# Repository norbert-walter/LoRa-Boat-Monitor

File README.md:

## LoRa Boat Monitor

Image: LoRa Boat Monitor

Project home page: https://open-boat-projects.org/en/lora-bootsmonitor/

The LoRa boat monitor is used to monitor the boat when it is absent. Various measured values are continuously recorded at freely adjustable time intervals and transferred to the [LoRaWAN](https://www.lora-wan.de/) forwarded. The data is from the TTN server ([The Thinks Network](https://thethingsnetwork.org/)) received in Amsterdam and cached and then sent to [Ubidots](https://ubidots.com/) forwarded as a web frontend. The data transmission is secured by encryption up to Ubidots. The measured data is displayed in Ubidots and various notifications can be sent by email when measured values are exceeded.

There are a large number of [LoRa gateways](https://thethingsnetwork.org/map) which can receive the sent measurement data and forward it to the TTN server. Many LoRa gateways are run by private individuals on a non-profit basis. Anyone who wants can operate their own gateway and make it available to the general public. The radio technology uses the license-free frequency range around 868 MHz and uses a special transmission technology (chirp) to achieve large ranges of up to 50 km at low data rates. The ranges depend on the type of transmission, the antenna height and the environment. In built-up areas such as cities, typical ranges of 1… 4 km are possible. In open environments such as lakes and the sea, up to 50 km can be reached. There are no costs for data transmission when sending LoRa telegrams. This is the big difference to other long range transmission technologies like [SIGFOX](https://www.sigfox.com/) and mobile data networks such as 3G / 4G / 5G. If no LoRa gateway is within range, a simple 1-channel or 3-channel LoRa gateway can be set up with the same board. Only a few components are then left out and a different firmware used. Alternatively, the measured values can also be sent directly to Ubidots via WLAN, provided that a WLAN is within range.

Image: LoRa data transmission Semtech GmbH

Image: Block diagram LoRa boat monitor

## The LoRa boat monitor has the following functions:

* 10… 32V supply voltage
* 1.2W power consumption
* LoRa transmitter and receiver with OLED display
* 868 MHz, SF7… SF12, 100 mW transmission power
* Dynamic spreeding factor adjustable SF7… FS10
* Supports channel 0...7 dynamic and fix
* Data transfer rate: 0.3 to 50 kbit / s
* Max. Telegram length for user data: 200 bytes
* Range: built-up area 1… 4km, open area up to 50km
* LoRa transmission interval 30s… 2.1h
* One-channel, three-channel and eight-channel modes can be set
* Feeding the data into The Thinks Network (TTN)
* Parameterization of the LoRa boat monitor possible via return channel (channel, SF, transmission interval, relay)
* WLAN (2.4 GHz) for alternative data transmission
* Web interface for operation
* Firmware update possible via WLAN and Internet
* GPS sensor for geographic location coordinates
* BME280 for measuring temperature, humidity and air pressure
* 1x battery voltage measurement (0… 32V service battery)
* 1x potential-free alarm contact eg for bilge and door monitoring
* 2x tank sensors (0 ... 180 Ohm) with percentage display
* Calibratable tank and voltage sensors
* 1x Reais output for potential-free switching of loads with specified time (5min ... 21h) up to 3A (12V or 230V)
* 2x 1Wire connection for temperature sensors DS18B20 for battery monitoring and refrigerator
* Monitoring and alerting via Ubidots web frontend
* Alerting by e-mail if limit values are exceeded via Ubidots
* Automatic data storage for the last 31 days at Ubidots
* Use of cheap embedded modules
* No SMD components on the board and easy to build
* Board can be ordered here:[https://aisler.net/p/GEIYWWXZ](https://aisler.net/p/GEIYWWXZ)
* Android app

## Create your own code

You have the option of creating your own code using the online [software development environment Gitpod](https://gitpod.io/#https://github.com/norbert-walter/LoRa-Boat-Monitor). Follow this link and a finished development environment similar to PlatformIO will be created that runs in your browser with all code components. To compile the software, enter ***bash run*** in the terminal. In the workspace you will find the compiled binary code under ***.pio/build/heltec_wifi_lora_32_V2/firmware.bin***. With a right click you can download the binary file. You need a account for Gitpod.
## Device flash process

With the [Web Flash Tool](https://norbert-walter.github.io/LoRa-Boat-Monitor/flash_tool/esp_flash_tool.html) you can very easily flash the device with the firmware from the web browser. You need a Chrome or Edge browser and a USB connection cable. If the device is connected to the USB port of the computer, the serial connection can be selected and the flash process can then be started.

## How can I use it?

## What is the current status?

I have completed many tasks but still not everything is perfect so far.

- [x] Technical recherche
- [x] Evaluation of function
    - [x] LoRa trasmission tests
    - [x] Accessibility of gateways
    - [x] Measurement of telegram losses 
    - [x] Test spreeding factors
    - [x] Antenna test
    - [x] TTN configuration
    - [x] Ubitots configutarion and restrictions
- [x] Mechanical design
    - [x] 3D parts für Onshape
- [x] Electronic design
    - [x] Circuit design
    - [x] Board design
    - [x] Customer sample circuit
- [ ] Software
    - [x] Basic functionality for LoRa
    - [x] LoRa back channel for configuration
    - [x] Dynamic spreedung factor
    - [x] Voltage measurement
    - [x] Tank sensors
    - [x] GPS modul
    - [x] BME280
    - [x] Alarm sensors
    - [x] Relay function
    - [x] JSON
    - [x] Web-Updater
    - [x] Web-Configurator
    - [x] Web server as data display
    - [x] VE.Direct support for Victron
    - [ ] Ubidots connection via WiFi
    - [x] NMEA0183 WiFi
    - [x] NMEA0183 Serial
    - [ ] MQTT
    - [x] Andoid App
    - [x] LoRa gateway firmware
    - [x] Migration to TTS V3
- [x] Components ordering
    - [x] Electronic board
    - [x] Mechanical parts
    - [x] Fittings
- [x] Prototyp creation
    - [x] LoRa boat monitor
    - [x] LoRa gateway
- [ ] Production Zero series
    - [ ] DIY Kits
    - [x] Assembled LoRa boat monitor
- [x] Shipping Zero Series
- [x] Documentation
    - [x] Documentation and update server on GitLab
    - [x] Technical description
    - [x] Construction manual
    - [x] Part list
    - [x] User manual
    - [x] Data sheet
    - [x] Flash instructions
- [x] Application tests
    - [x] Temperature 20...40°C
    - [x] LoRa range test (SF7...SF12)
    - [x] WiFi stability test
    - [x] Connection test
    - [x] Long time test
    - [x] User experiences
- [ ] Extensions
    - [ ] Battery current sensor
    - [ ] Actions and alarms depends on events and measuring values
    - [ ] Build a LoRa gateway structure on two towers for the IJsselmeer in Netherlands 
- [ ] Certification
    - [ ] CE Certification

## Questions?

For questions or suggestions please get in contact via email at norbert-walter(at)web.de.

If you like to help or consider this project useful, please donate. Thanks for your support!

[Donate with PayPal](https://www.paypal.com/cgi-bin/webscr?cmd=_s-xclick&hosted_button_id=5QZJZBM252F2L)

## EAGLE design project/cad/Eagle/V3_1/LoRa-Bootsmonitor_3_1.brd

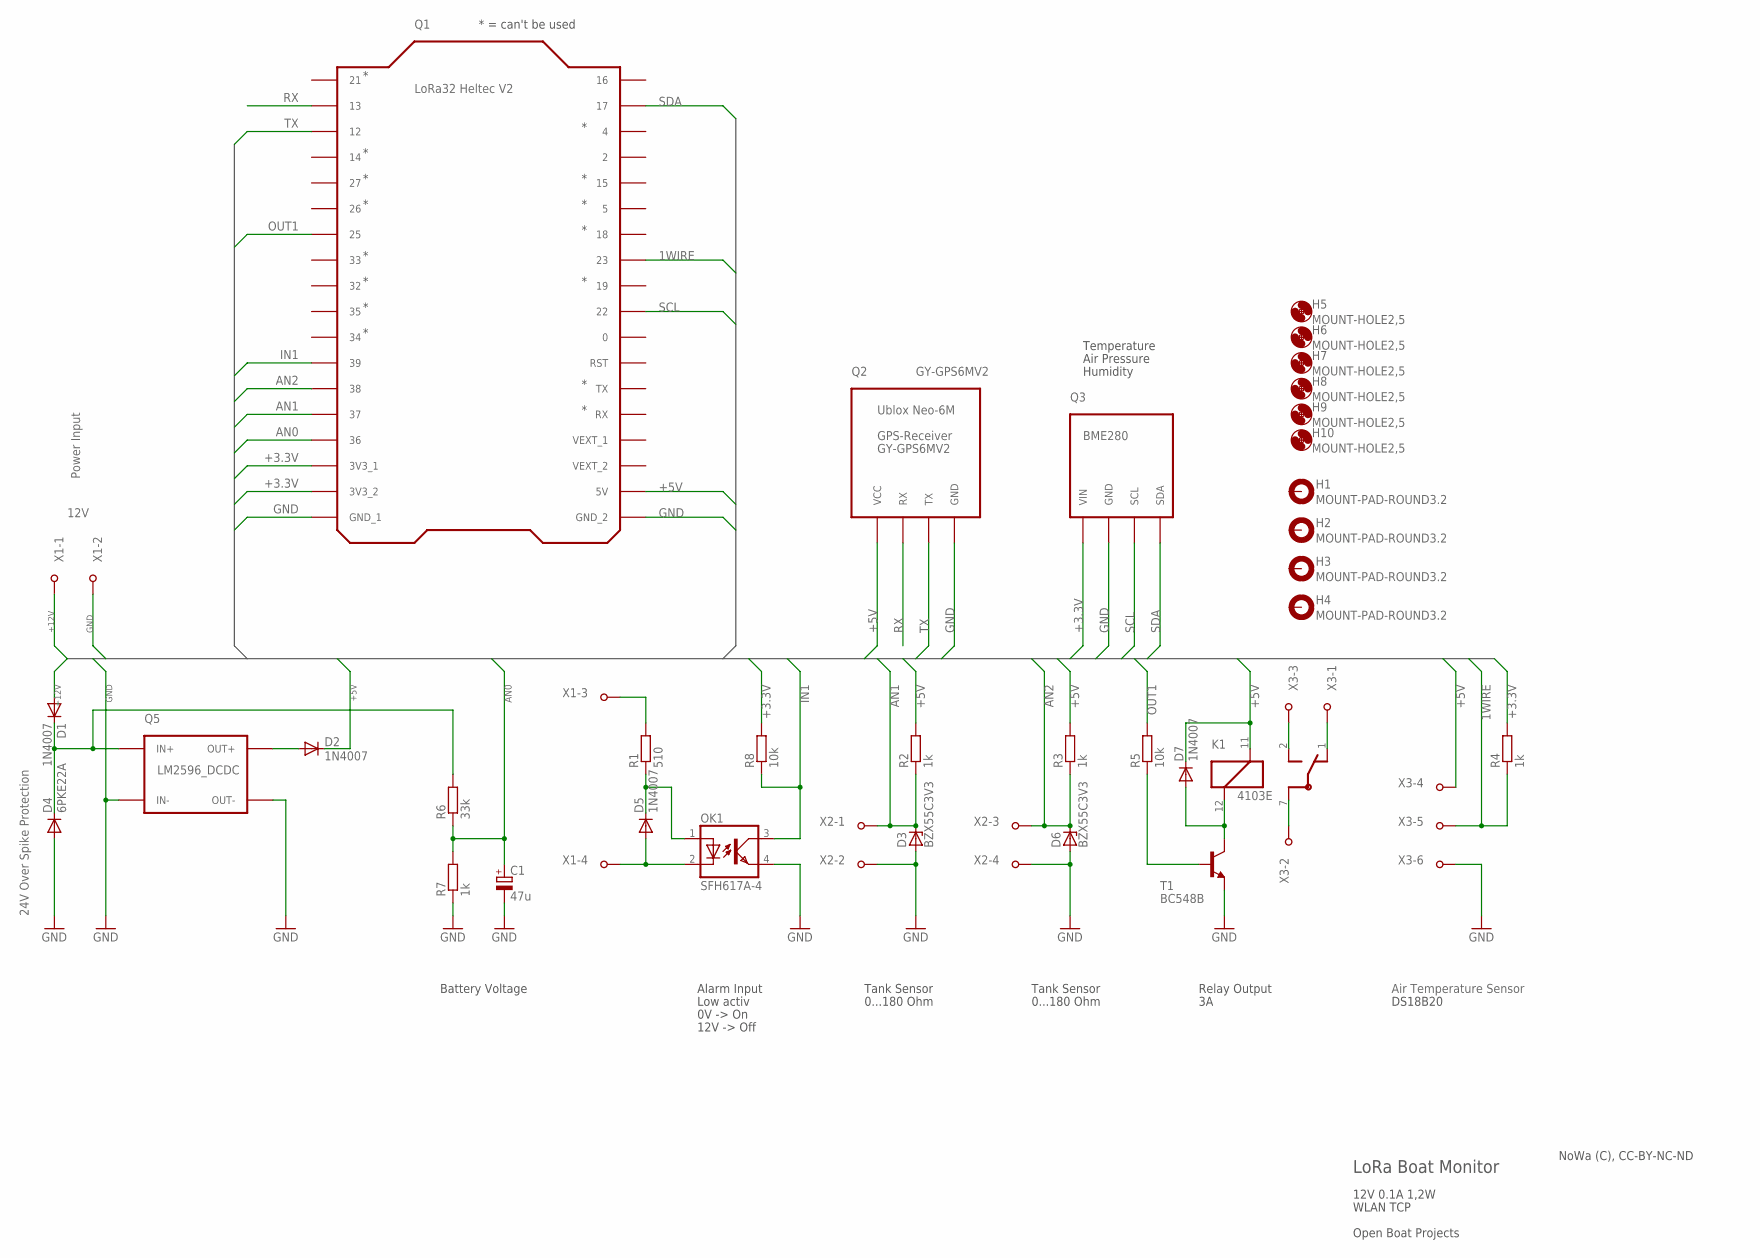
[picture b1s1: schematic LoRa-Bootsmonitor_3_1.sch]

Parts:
C1: 47u; E3,5-8
D1, D2, D5, D7: 1N4007; SOD81
D3, D6: BZX55C3V3; DO35Z10
D4: 6PKE22A; DO201-15
H1, H2, H3, H4: MOUNT-PAD-ROUND3.2; 3,2-PAD
H5, H6, H7, H8, H9, H10: MOUNT-HOLE2,5; 2,5
K1: 4103E; RELAIS_4102E
OK1: SFH617A-4; DIL04
Q1: LORA32_HELTEC_V2
Q2: GY-GPS6MV2; GY_GPS6MV2_H
Q3: BME280
Q5: LM2596_DCDC
R1: 510; 0207/10
R2, R3, R4, R7: 1k; 0207/10
R5, R8: 10k; 0207/10
R6: 33k; 0207/10
T1: BC548B; TO92-EBC
X1, X2: AKL_092_04
X3: AKL_092_06

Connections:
1WIRE: Q1.11 (23), R4.1, X3.5
+3.3V: Q1.34 (3V3_1), Q1.35 (3V3_2), Q3.VIN, R4.2, R8.2
+5V: D2.C, D7.C, K1.11, Q1.2 (5V), Q2.VCC, R2.2, R3.2, X3.4
+12V: D1.A, X1.1
AN0: C1.+, Q1.33 (36), R6.1, R7.2
AN1: D3.C, Q1.32 (37), R2.1, X2.1
AN2: D6.C, Q1.31 (38), R3.1, X2.3
GND: C1.-, D3.A, D4.A, D6.A, OK1.4 (EMIT), Q1.1 (GND_2), Q1.36 (GND_1), Q2.GND, Q3.GND, Q5.IN-, Q5.OUT-, R7.1, T1.E, X1.2, X2.2, X2.4, X3.6
IN1: OK1.3 (COL), Q1.30 (39), R8.1
unnamed: R5.1, T1.B
unnamed: D2.A, Q5.OUT+
unnamed: D7.A, K1.12, T1.C
unnamed: R1.2, X1.3
unnamed: D5.C, OK1.1 (A), R1.1
unnamed: D5.A, OK1.2 (C), X1.4
unnamed: D1.C, D4.C, Q5.IN+, R6.2
unnamed: K1.1, X3.1
unnamed: K1.2, X3.3
unnamed: K1.7, X3.2
OUT1: Q1.25, R5.2
RX: Q1.20 (13), Q2.RX
SCL: Q1.9 (22), Q3.SCL
SDA: Q1.17, Q3.SDA
TX: Q1.21 (12), Q2.TX

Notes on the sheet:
12V
LoRa Boat Monitor
12V 0.1A 1,2W
WLAN TCP
Power Input
24V Over Spike Protection
Air Temperature Sensor
Battery Voltage
Alarm Input
Relay Output
DS18B20
Tank Sensor
0...180 Ohm
Temperature
Air Pressure
Humidity
Open Boat Projects
NoWa (C), CC-BY-NC-ND
Low activ
0V -> On
12V -> Off
* = can't be used

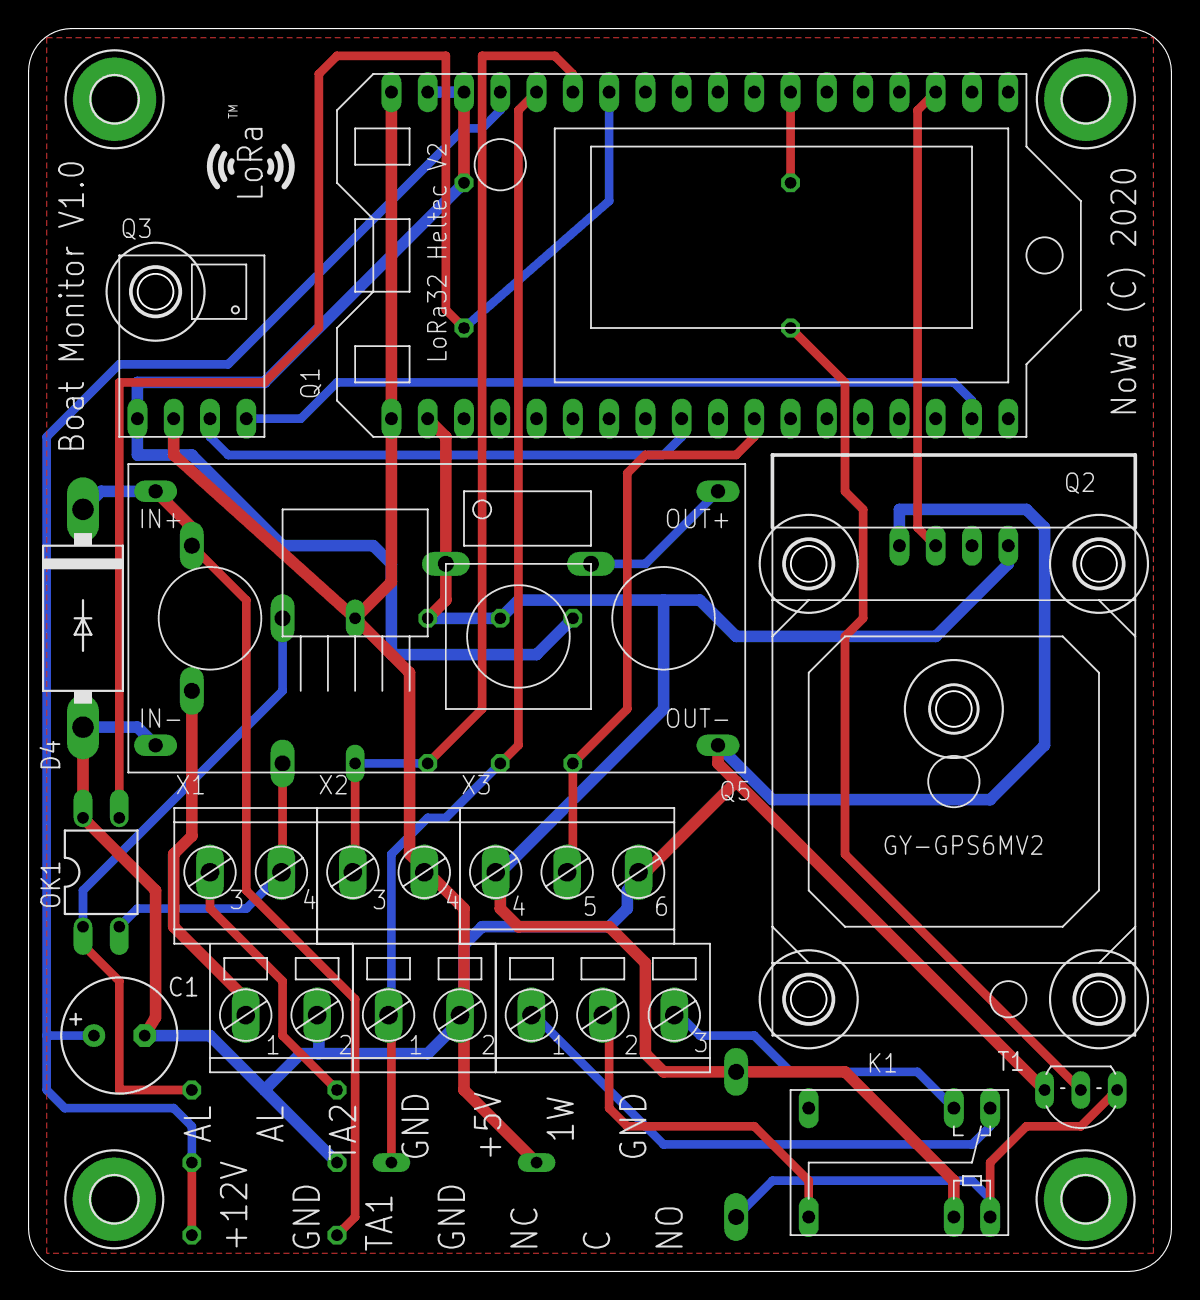
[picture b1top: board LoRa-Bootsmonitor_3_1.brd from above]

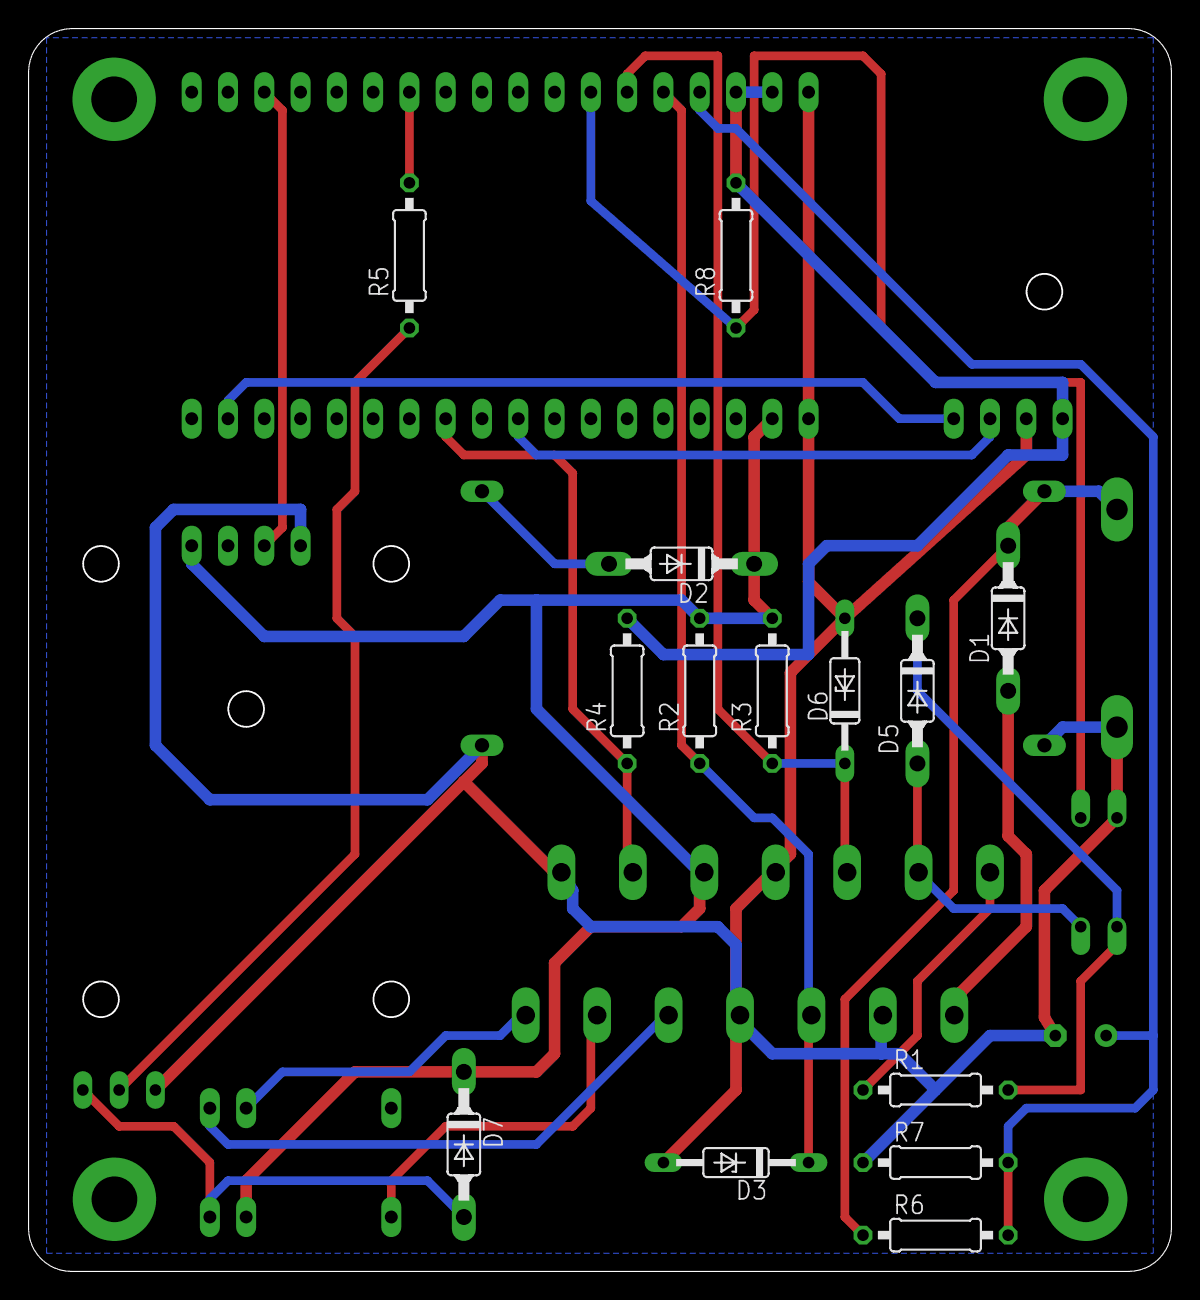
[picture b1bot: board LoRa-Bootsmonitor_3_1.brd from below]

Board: 2 copper layers, 79.9 x 86.9 mm, 36 parts (14 on the bottom side), 24 nets.

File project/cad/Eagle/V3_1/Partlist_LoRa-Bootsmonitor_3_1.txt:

Stueckliste

Menge Wert               Device              Bauteile               
2                        AKL_092_04          X1, X2                 
1                        AKL_092_06          X3                     
1                        LORA32_HELTEC_V2    Q1                     
4     1N4007             BYD13               D1, D2, D5, D7
1     500		         R-EU_0207/10        R1 
5     1k                 R-EU_0207/10        R2, R3, R4, R7     
1     5V                 RELAIS              K1                     
1     6PKE22A            1N4728              D4                     
1     10k                R-EU_0207/10        R5, R8                     
1     33k                R-EU_0207/10        R6                     
1     47u                CPOL-EUE5-8.5       C1                     
1     BC557B             BC557B-PNP-TO92-EBC T1                     
1     BME280             BME280              Q3                     
2     BZX55C3V3          BZX55               D3, D6                 
1     GY-GPS6MV2         GY_GPS6MV2_H        Q2                     
1     LM2596_DCDC        LM2596_DCDC         Q5                     
6     MOUNT-HOLE2,5      MOUNT-HOLE2,5       H5, H6, H7, H8, H9, H10
4     MOUNT-PAD-ROUND3.2 MOUNT-PAD-ROUND3.2  H1, H2, H3, H4         
1     SFH617A-4          SFH610              OK1

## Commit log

2023-03-10 Change for variable name crypt
2023-03-10 Add project informations and data
2023-03-10 changes for gitpod
2023-03-11 chages
2023-03-11 Update run
2023-03-12 new docs structure
2023-03-12 add online docu
2023-03-12 set new links to github
2023-03-12 add new docu
2023-03-12 fix run shell script
2023-03-17 static libs
2023-03-17 compiler run gitpod
2023-03-17 change to fix Esperssif SDK 3.4.0
2023-03-18 wifi pw regexp
    character "-" now allowed for wifi pw.
2023-03-31 change file name
2023-03-31 Fix for DS18B20
2023-03-31 change offset in formatter
2023-03-31 new files for flash tools
2023-03-31 New documentation
2023-03-31 New online doku for V1.06
2023-04-06 implement sleep mode (beta)
    Implemented sleep mode.
    Pin39 will control mode.
    - platformio.ini: changed lmic lib from IBM to MCCI, added lib config into platformio.ini (IBM version is deprecated and doesn't support return of scheduled jobs).
    - lora.h: added support for sleep mode.
    - LoRa_boat_monitor_abp.cpp: added state machein for sleep mode.
    - task.h: due to some error the task will be disabled for first tests.
2023-04-07 minor changes
    Moved wifi functions from setup into state1.
2023-04-08 minor changes
    - Functions.h: split debug messages into different topics. In the beginning of the function will be booleans to control.
    - LoRa_boat_monitor_abp.cpp: fixed double wifi config.
2023-04-11 minor changes.
    - Changed Lora counter from "Counter16" into "LMIC.seqnoUp"
    - LoRa.h: "DebugPrint" in "do_send" can be disabled. "EV_TXSTAT" as Event DebugPrint added.
    - LoRa_boat_monitor_abp.cpp: some lora optimizations.
2023-04-12 rename payload files from "*.h" into "*.js"
2023-04-15 minor changes
    - Configuration.h: changed the Wifi SSID
    - serveral files: added options for Standby mode and Lora Standby mode (only in standby or always)
    - lora.h: modify the debug options.
    - put lora send into task on core0
2023-04-18 minor changes
    Activate the VE functions.
2023-05-08 Update Partlist_LoRa-Bootsmonitor_3.txt
    Fix errors
2023-07-20 Update platformio.ini
    change lib U8g2
2023-07-20 change lib for U8g2
2023-12-20 Update README.md
    Change link
2023-12-20 Update README.md
    Changes
2024-06-10 smal changes
2024-06-10 update readme.md from main branch
2025-07-22 Update platformio.ini
    Add build flag for LoRa frequencies
2025-12-17 Add devcontainer environment as replace for Gitpod
2025-12-17 Modify paltformio.ini for devcontainer environment

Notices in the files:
project/cad/Eagle/V3_1/LoRa-Bootsmonitor_3_1.brd:
NoWa (C) 2020
